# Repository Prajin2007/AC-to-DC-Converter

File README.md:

# ⚡ AC to DC Converter PCB

A full-wave bridge rectifier circuit designed in KiCad, converting AC mains input to filtered DC output with a power indicator LED.

---

##  Overview

This PCB implements a classic **full-wave bridge rectifier** using four 1N4007 diodes, a 1000µF smoothing capacitor, and a power-on LED indicator. Designed as a foundational power electronics project to learn KiCad schematic capture and PCB layout.

---

## 🔧 Specifications

| Parameter | Value |
|:----------|:------|
| Topology | Full-wave Bridge Rectifier |
| Input | AC (via screw terminal J1) |
| Output | Filtered DC (via screw terminal J2) |
| Rectifier Diodes | 4x 1N4007 |
| Filter Capacitor | 1000µF electrolytic |
| Power Indicator | LED (D5) with 2.2k series resistor |
| Bleeder Resistor | 10k (R2) |
| EDA Tool | KiCad |

---

## 🧠 How It Works

```
AC Input (J1)
     │
     ▼
┌─────────────────┐
│  Bridge Rectifier│  ← D1, D2, D3, D4 (1N4007)
│  (Full-wave)     │     converts AC → pulsating DC
└────────┬────────┘
         │
         ▼
   ┌─────────┐
   │  C1     │  ← 1000µF smoothing capacitor
   │ 1000µF  │     reduces ripple voltage
   └────┬────┘
        │
        ├──── R1 (2.2k) + D5 (LED) → Power indicator
        │
        ├──── R2 (10k) → resistor (discharges cap safely)
        │
        ▼
  DC Output (J2)
```

1. **Bridge rectifier** — four 1N4007 diodes arranged so both halves of the AC cycle contribute to DC output
2. **Filter capacitor** — 1000µF electrolytic smooths the pulsating DC into steady DC
3. **LED indicator** — lights up when DC output is present, with 2.2k current-limiting resistor
4. **Bleeder resistor** — 10k resistor safely discharges the capacitor when power is removed

---

## 🧩 Bill of Materials

| Ref | Component | Value | Package |
|:----|:----------|:------|:--------|
| D1, D2, D3, D4 | Rectifier Diode | 1N4007 | DO-41 |
| D5 | LED | Any colour | 5mm / 3mm |
| C1 | Electrolytic Capacitor | 1000µF | Radial |
| R1 | Resistor | 2.2k | 0805 / Through-hole |
| R2 | Resistor | 10k | 0805 / Through-hole |
| J1 | Screw Terminal | AC Input | ScreW_Terminal_01x02 |
| J2 | Screw Terminal | DC Output | Screw_Terminal_01x02 |

---

## 🖼️ Screenshots

### Schematic

### PCB Layout

### 3D Render

---

## 🛠️ Tools Used

---

## 📚 What I Learned

- KiCad schematic capture and symbol placement
- Full-wave bridge rectifier theory and component selection
- Filter capacitor sizing for ripple reduction
- PCB layout, component footprint assignment and DRC
- Exporting Gerber files for manufacturing

---

## 👤 Author

**Prajin S**
B.Tech Electronics and Instrumentation Engineering, VIT Vellore

---

*First KiCad PCB design — part of my electronics learning journey.*

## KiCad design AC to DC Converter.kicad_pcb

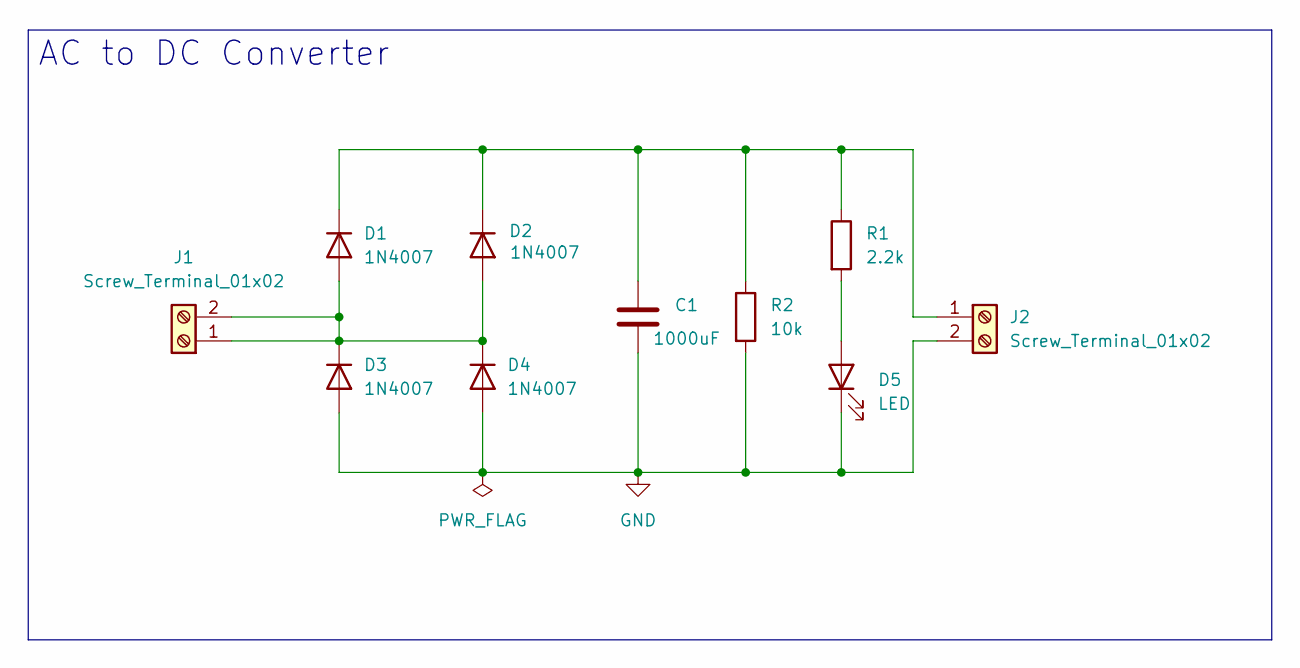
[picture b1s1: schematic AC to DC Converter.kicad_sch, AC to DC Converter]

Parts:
C1: 1000uF; C_Radial_D8.0mm_H11.5mm_P3.50mm
D1, D2, D3, D4: 1N4007; D_DO-41_SOD81_P10.16mm_Horizontal
D5: LED; LED_D5.0mm
J1, J2: Screw_Terminal_01x02; TerminalBlock_Phoenix_MKDS-3-2-5.08_1x02_P5.08mm_Horizontal
R1: 2.2k; R_Axial_DIN0207_L6.3mm_D2.5mm_P7.62mm_Horizontal
R2: 10k; R_Axial_DIN0207_L6.3mm_D2.5mm_P7.62mm_Horizontal

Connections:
GND: C1.2, D3.2 (A), D4.2 (A), D5.1 (K), J2.2, R2.2
unnamed: D1.2 (A), D2.2 (A), D3.1 (K), D4.1 (K), J1.1, J1.2
unnamed: C1.1, D1.1 (K), D2.1 (K), J2.1, R1.1, R2.1
unnamed: D5.2 (A), R1.2

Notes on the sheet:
AC to DC Converter

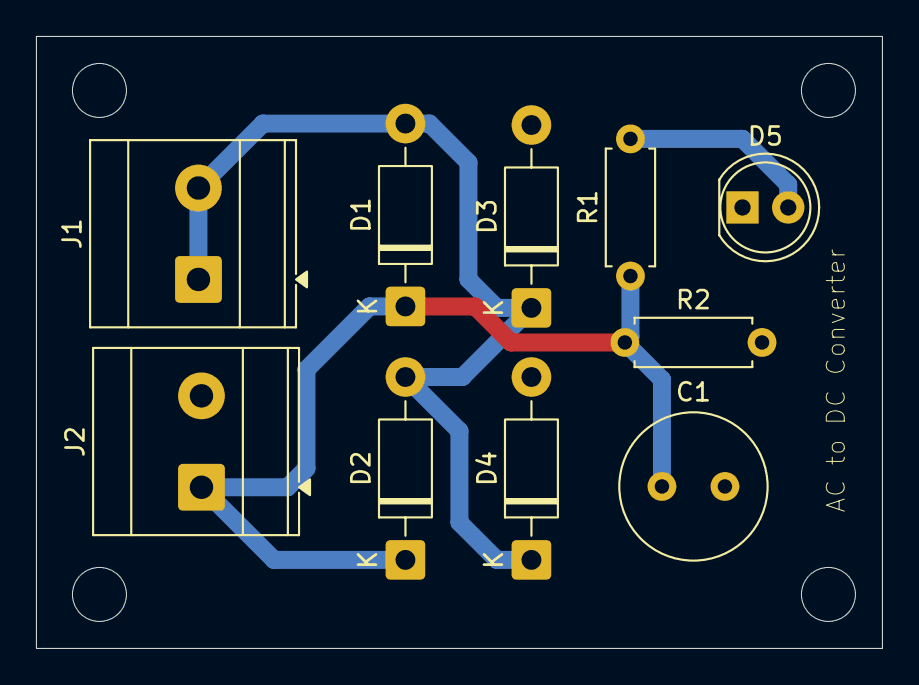
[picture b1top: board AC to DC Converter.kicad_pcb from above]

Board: 2 copper layers, 47.0 x 34.0 mm, 10 parts (0 on the bottom side), 4 nets.

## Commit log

2026-06-28 Create Images
